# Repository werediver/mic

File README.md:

# Microphone interface

A phantom-powered balanced interface for an [electret microphone](https://en.wikipedia.org/wiki/Electret_microphone) capsule with a built-in [JFET](https://en.wikipedia.org/wiki/JFET).

This interface has no gain, except for doubling the amplitude while converting the single-ended signal
from the capsule into a balanced output signal.

The PCB is designed to fit into a metal tube ⌀11.5 or wider.

Please note that two OPA1641 ICs are used in the design just because I already had them when designing the circuit. Using OPA1642 would be more space-efficient and I recommend you using OPA1642, not OPA1641 in your design.

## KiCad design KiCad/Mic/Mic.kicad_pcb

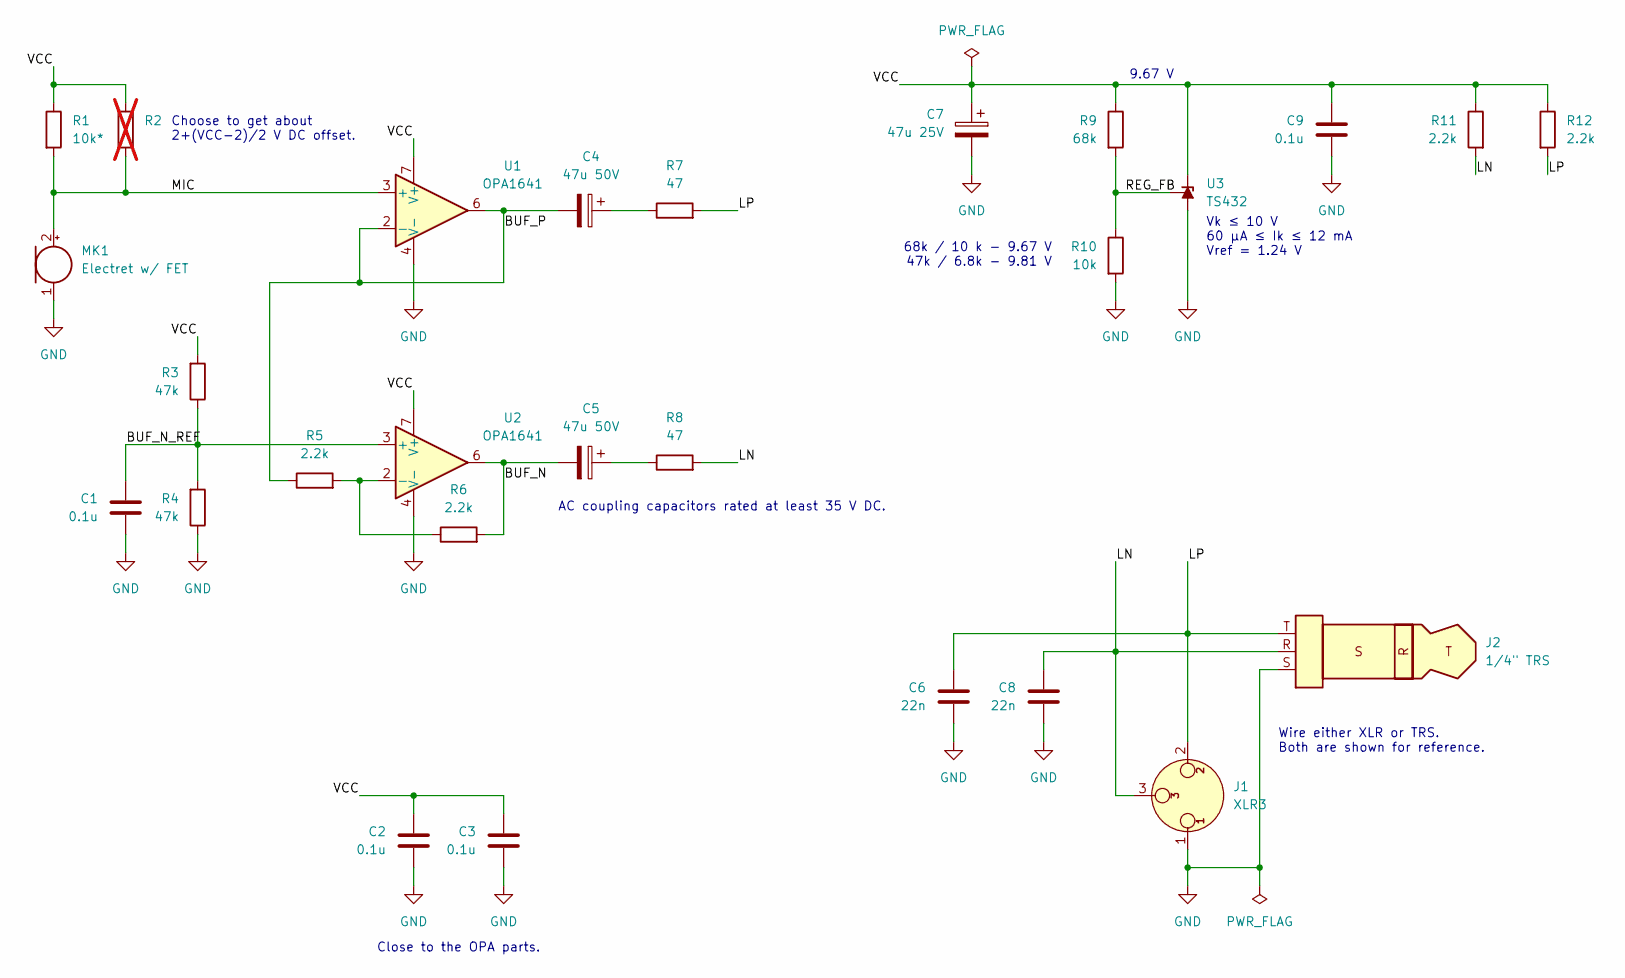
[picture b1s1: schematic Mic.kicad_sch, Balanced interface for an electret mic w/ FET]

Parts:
C1, C2, C3, C9: 0.1u; C_0805_2012Metric_Pad1.18x1.45mm_HandSolder
C4, C5: 47u 50V; CP_Elec_6.3x5.8
C6, C8: 22n; C_0805_2012Metric_Pad1.18x1.45mm_HandSolder
C7: 47u 25V; CP_EIA-7343-31_Kemet-D_Pad2.25x2.55mm_HandSolder
J1: XLR3; PinHeader_1x03_P2.54mm_Vertical
J2: 1/4" TRS
MK1: Electret w/ FET; PinHeader_1x02_P2.54mm_Vertical
R1: 10k*; R_0805_2012Metric_Pad1.20x1.40mm_HandSolder
R2: R_0805_2012Metric_Pad1.20x1.40mm_HandSolder; not fitted
R3, R4: 47k; R_0805_2012Metric_Pad1.20x1.40mm_HandSolder
R5, R6, R11, R12: 2.2k; R_0805_2012Metric_Pad1.20x1.40mm_HandSolder
R7, R8: 47; R_0805_2012Metric_Pad1.20x1.40mm_HandSolder
R9: 68k; R_0805_2012Metric_Pad1.20x1.40mm_HandSolder
R10: 10k; R_0805_2012Metric_Pad1.20x1.40mm_HandSolder
U1, U2: OPA1641; SOIC-8_3.9x4.9mm_P1.27mm
U3: TS432; SOT-23

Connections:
/BUF_N: C5.2, R6.2, U2.6
/BUF_N_REF: C1.1, R3.1, R4.2, U2.3 (+)
/BUF_P: C4.2, R5.1, U1.2 (-), U1.6
/LN: C8.1, J1.3, J2.R, R8.2, R11.2
/LP: C6.1, J1.2, J2.T, R7.2, R12.2
/MIC: MK1.2 (+), R1.2, R2.2, U1.3 (+)
/REG_FB: R9.2, R10.1, U3.1 (REF)
/VCC: C2.1, C3.1, C7.1, C9.1, R1.1, R2.1, R3.2, R9.1, R11.1, R12.1, U1.7 (V+), U2.7 (V+), U3.2 (K)
GND: C1.2, C2.2, C3.2, C6.2, C7.2, C8.2, C9.2, J1.1, J2.S, MK1.1 (-), R4.1, R10.2, U1.4 (V-), U2.4 (V-), U3.3 (A)
unnamed: C4.1, R7.1
unnamed: C5.1, R8.1
unnamed: R5.2, R6.1, U2.2 (-)

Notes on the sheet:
Wire either XLR or TRS. Both are shown for reference.
68k / 10 k - 9.67 V 47k / 6.8k - 9.81 V
Choose to get about 2+(VCC-2)/2 V DC offset.
AC coupling capacitors rated at least 35 V DC.
Close to the OPA parts.
9.67 V
Vk ≤ 10 V 60 μA ≤ Ik ≤ 12 mA Vref = 1.24 V

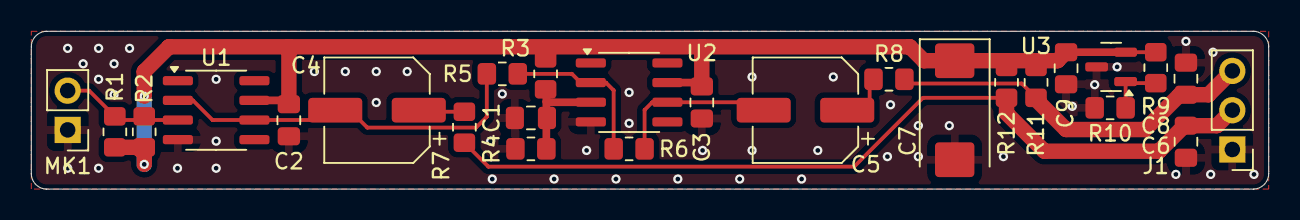
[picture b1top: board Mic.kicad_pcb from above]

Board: 2 copper layers, 80.0 x 10.2 mm, 26 parts (0 on the bottom side), 12 nets.

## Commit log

2024-06-20 Add the first revision of the mic interface
2024-07-02 Minor updates to the scematic and the PCB
